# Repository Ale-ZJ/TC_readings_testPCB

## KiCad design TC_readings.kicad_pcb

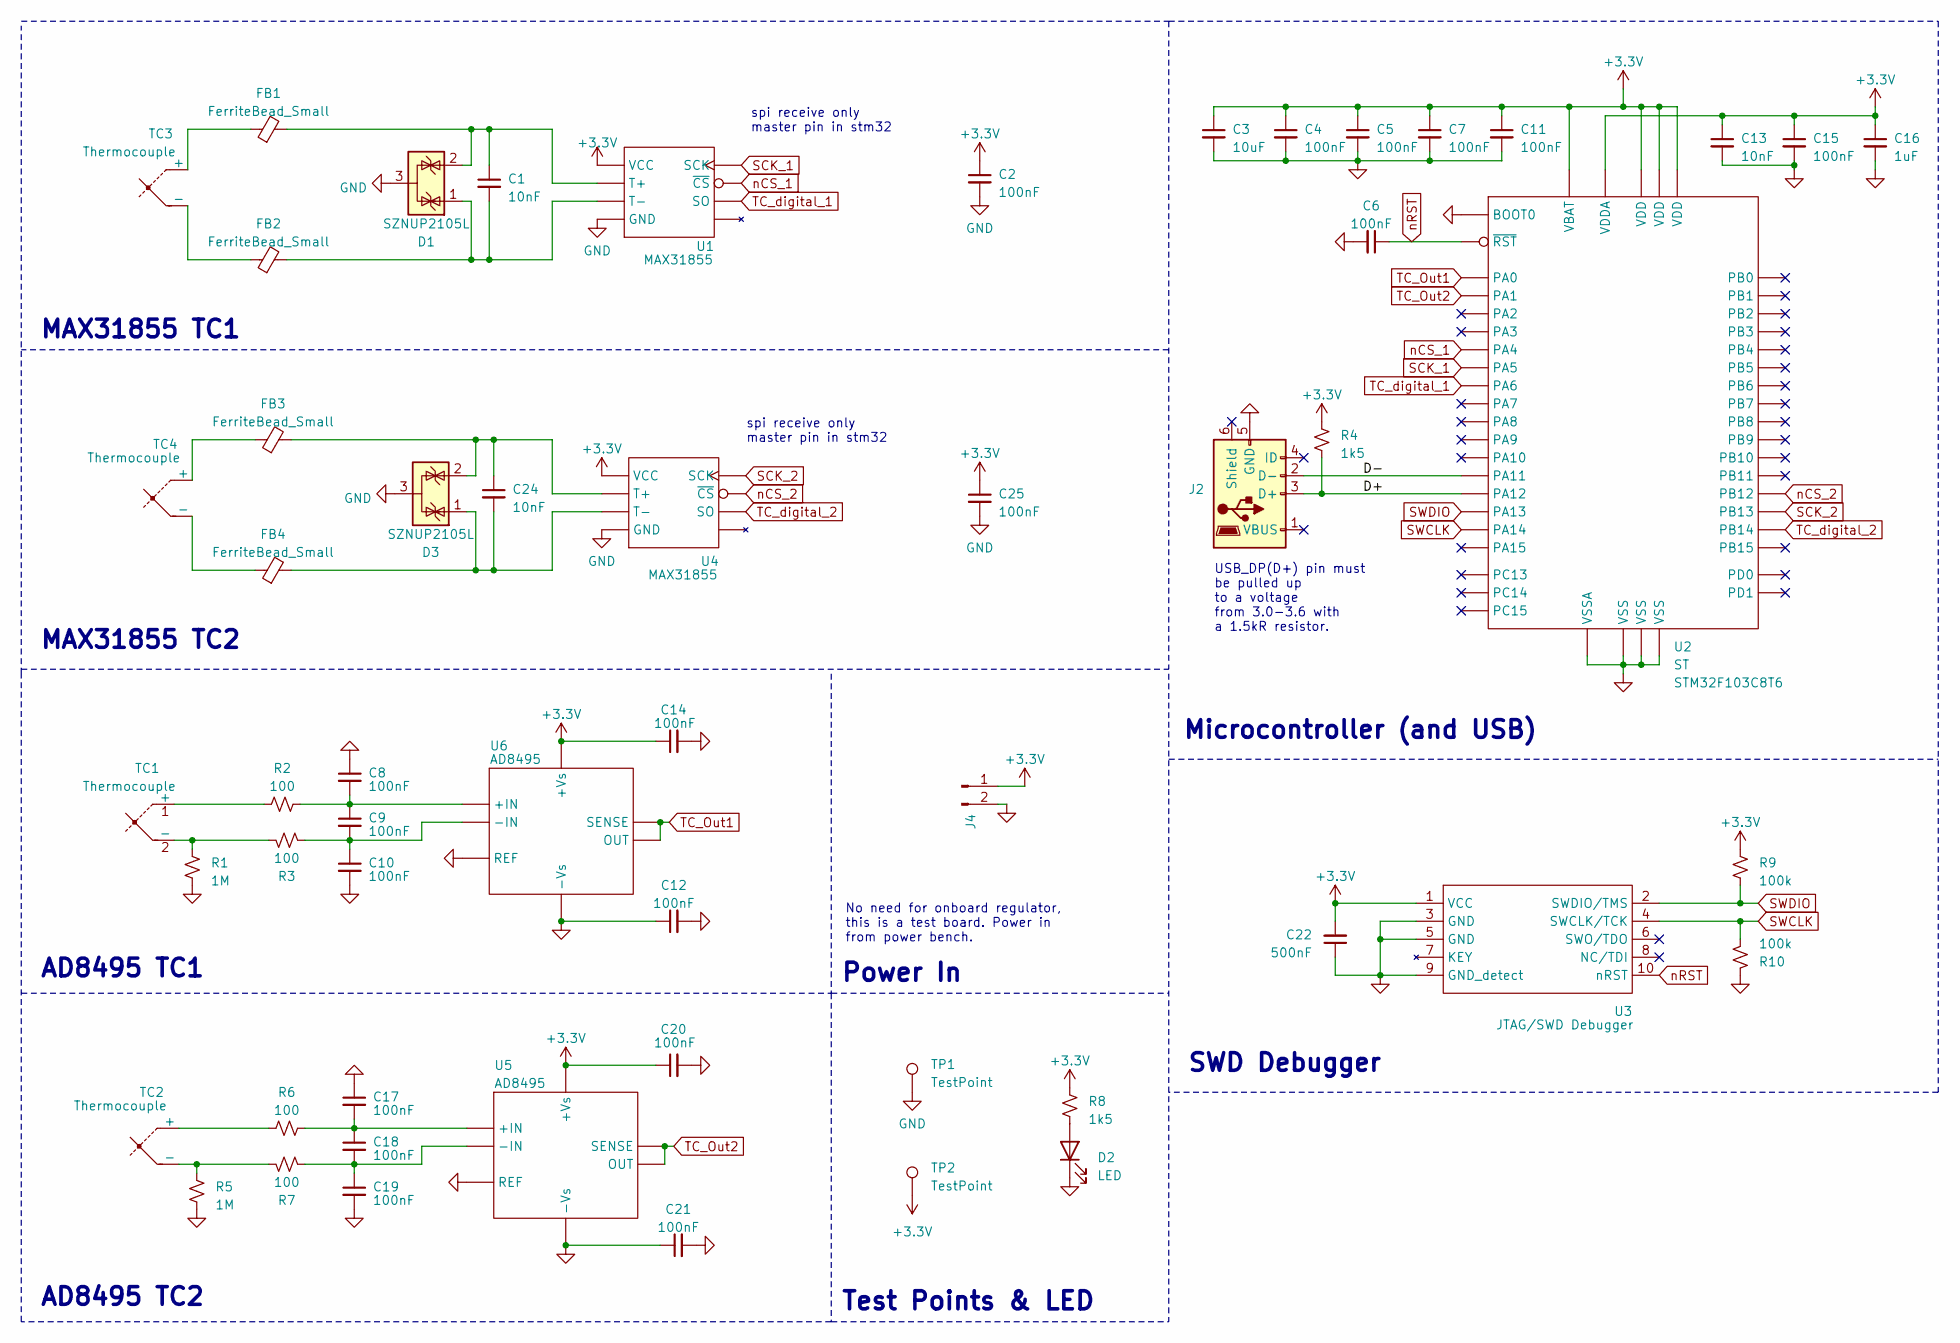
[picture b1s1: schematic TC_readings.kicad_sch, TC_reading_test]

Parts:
C1, C13, C24: 10nF; C_0402_1005Metric
C2, C4, C5, C6, C7, C8, C9, C10, C11, C12, C14, C15, C17, C18, C19, C20, C21, C25: 100nF; C_0402_1005Metric
C3: 10uF; C_0402_1005Metric
C16: 1uF; C_0603_1608Metric
C22: 500nF; C_0402_1005Metric
D1, D3: SZNUP2105L; SOT-23
D2: LED; LED_0603_1608Metric
FB1, FB2, FB3, FB4: FerriteBead_Small; L_0603_1608Metric
J2: USB_B_Micro; USB_Micro-B_Wuerth_629105150521
J4: Conn_01x02_Pin; TerminalBlock_bornier-2_P5.08mm
R1, R5: 1M; R_0805_2012Metric
R2, R3, R6, R7: 100; R_0402_1005Metric
R4, R8: 1k5; R_0603_1608Metric
R9, R10: 100k; R_0603_1608Metric
TC1, TC2, TC3, TC4: Thermocouple; TerminalBlock_bornier-2_P5.08mm
TP1, TP2: TestPoint; TestPoint_Pad_D2.0mm
U1, U4: SOIC-8_3.9x4.9mm_P1.27mm; Part # MAX31855
U2: LQFP-48_7x7mm_P0.5mm; Part # STM32F103C8T6
U3: PinHeader_2x05_P2.54mm_Vertical; Part # JTAG/SWD Debugger
U5, U6: MSOP-8_3x3mm_P0.65mm; Part # AD8495

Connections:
+3.3V: C2.1, C3.1, C4.1, C5.1, C7.1, C11.1, C13.1, C14.1, C15.1, C16.1, C20.1, C22.2, C25.1, J4.1, R4.1, R8.2, R9.1, U1.4 (VCC), U2.1 (VBAT), U2.9 (VDDA), U2.24 (VDD), U2.36 (VDD), U2.48 (VDD), U3.1 (VCC), U4.4 (VCC), U5.7 (+Vs), U6.7 (+Vs); also elsewhere on the board
/D+: J2.3 (D+), R4.2, U2.33 (PA12)
/D-: J2.2 (D-), U2.32 (PA11)
GND: C2.2, C3.2, C4.2, C5.2, C6.2, C7.2, C8.1, C10.2, C11.2, C12.1, C12.2, C13.2, C14.2, C15.2, C16.2, C17.1, C19.2, C20.2, C21.1, C21.2, C22.1, C25.2, D1.3 (A), D3.3 (A), J2.5 (GND), J4.2, R1.1, R5.1, R10.1, U1.1 (GND), U2.8 (VSSA), U2.23 (VSS), U2.35 (VSS), U2.44 (BOOT0), U2.47 (VSS), U3.3 (GND), U3.5 (GND), U3.9 (GND_detect), U4.1 (GND), U5.2 (REF), U5.3 (-Vs), U6.2 (REF), U6.3 (-Vs); also elsewhere on the board
unnamed 4: R8.1; also elsewhere on the board
unnamed: R2.1, TC1.1 (+)
unnamed: R1.2, R3.1, TC1.2 (-)
unnamed: R6.1, TC2.1 (+)
unnamed: R5.2, R7.1, TC2.2 (-)
unnamed: FB1.1, TC3.1 (+)
unnamed: FB2.1, TC3.2 (-)
unnamed: FB3.1, TC4.1 (+)
unnamed: FB4.1, TC4.2 (-)
unnamed: C1.1, D1.2 (K), FB1.2, U1.3 (T+)
unnamed: C1.2, D1.1 (K), FB2.2, U1.2 (T-)
unnamed: C24.1, D3.2 (K), FB3.2, U4.3 (T+)
unnamed: C24.2, D3.1 (K), FB4.2, U4.2 (T-)
unnamed: C17.2, C18.1, R6.2, U5.8 (+IN)
unnamed: C18.2, C19.1, R7.2, U5.1 (-IN)
unnamed: C8.2, C9.1, R2.2, U6.8 (+IN)
unnamed: C9.2, C10.1, R3.2, U6.1 (-IN)
SCK_1: U1.5 (SCK), U2.15 (PA5)
SCK_2: U2.26 (PB13), U4.5 (SCK)
SWCLK: R10.2, U2.37 (PA14), U3.4 (SWCLK/TCK)
SWDIO: R9.2, U2.34 (PA13), U3.2 (SWDIO/TMS)
TC_Out1: U2.10 (PA0), U6.5 (SENSE), U6.6 (OUT)
TC_Out2: U2.11 (PA1), U5.5 (SENSE), U5.6 (OUT)
TC_digital_1: U1.7 (SO), U2.16 (PA6)
TC_digital_2: U2.27 (PB14), U4.7 (SO)
nCS_1: U1.6 (~CS), U2.14 (PA4)
nCS_2: U2.25 (PB12), U4.6 (~CS)
nRST: C6.1, U2.7 (~RST), U3.10 (nRST)

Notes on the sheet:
AD8495 TC1
Microcontroller (and USB)
MAX31855 TC2
Test Points & LED
spi receive only master pin in stm32
USB_DP(D+) pin must be pulled up to a voltage from 3.0-3.6 with a 1.5kR resistor.
No need for onboard regulator, this is a test board. Power in from power bench.
SWD Debugger
Power In
AD8495 TC2
MAX31855 TC1

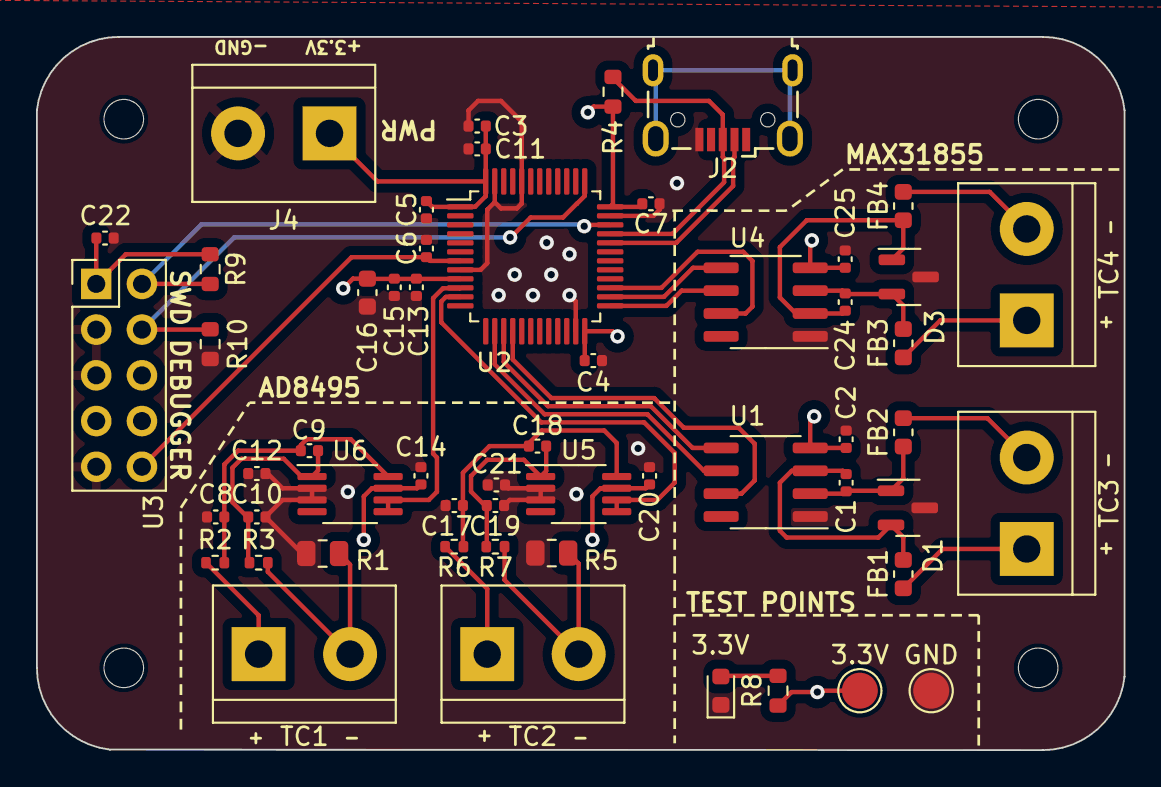
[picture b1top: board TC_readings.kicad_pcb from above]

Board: 4 copper layers, 60.4 x 39.6 mm, 55 parts (0 on the bottom side), 32 nets.

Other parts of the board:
3.3V: TestPoint; TestPoint_Pad_D2.0mm
3.3V#2: LED; LED_0603_1608Metric
GND: TestPoint; TestPoint_Pad_D2.0mm

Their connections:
+3.3V: 3.3V.1; also elsewhere on the board
GND: 3.3V#2.1 (K), GND.1; also elsewhere on the board
unnamed 4: 3.3V#2.2 (A); also elsewhere on the board

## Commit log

2023-10-26 Add gitignore
2023-10-30 Change to 4 layers
2023-11-03 TC Reading Test V1.0
2023-12-07 Add RTD reading sensor
